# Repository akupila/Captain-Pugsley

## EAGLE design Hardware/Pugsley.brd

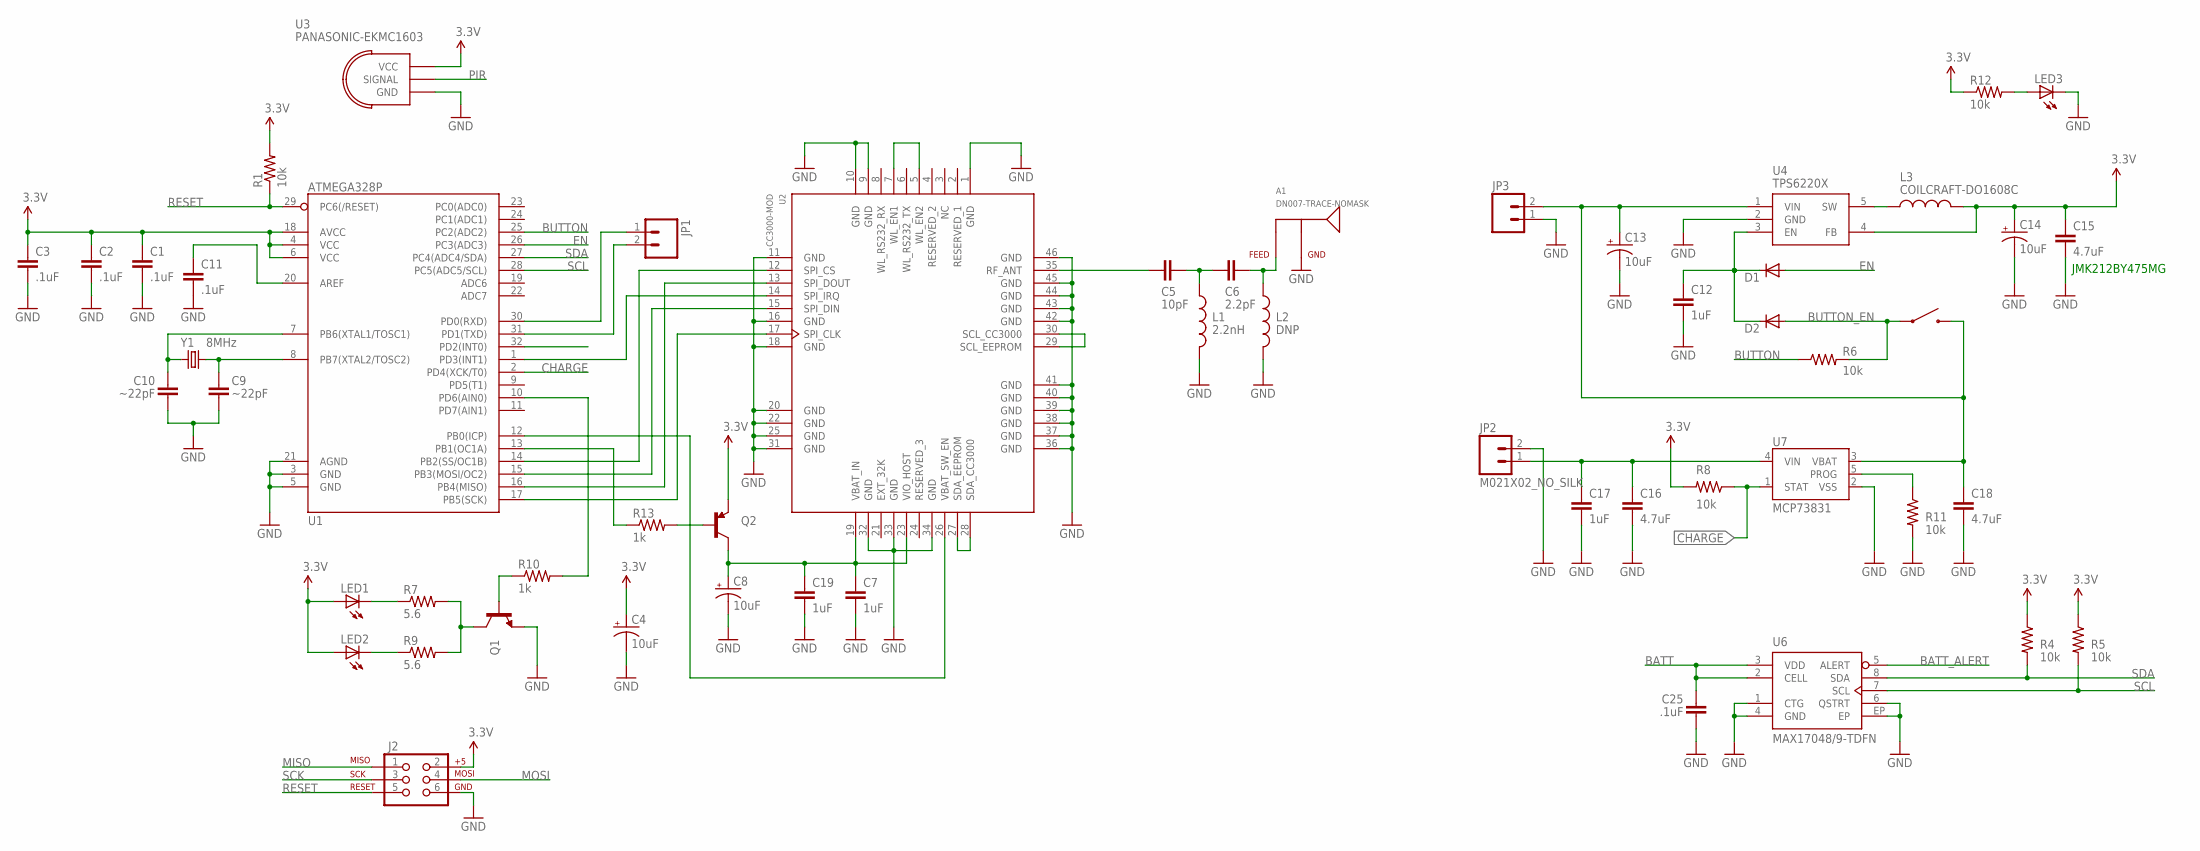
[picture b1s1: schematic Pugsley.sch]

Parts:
A1: DN007-TRACE-NOMASK
C1, C2, C3, C11, C25: .1uF; 0402-CAP
C4, C8, C13, C14: 10uF; EIA3216
C5: 10pF; 0402-CAP
C6: 2.2pF; 0402-CAP
C7, C12, C17, C19: 1uF; 0402-CAP
C9, C10: ~22pF; 0402-CAP
C15, C16, C18: 4.7uF; 0805
D1, D2: DIODESOD; SOD-323
J2: AVR_SPI_PRG_6NS; 2X3-NS
JP1, JP2, JP3: M021X02_NO_SILK; 1X02_NO_SILK
L1: 2.2nH; C0402
L2: DNP; C0402
L3: COILCRAFT-DO1608C
LED1, LED2, LED3: LED0603; LED-0603
Q1: TRANSISTOR_NPNSOT23; SOT23
Q2: TRANSISTOR_PNPSMD; SOT23-3
R1, R4, R5, R6, R8, R11, R12: 10k; 0402-RES
R7, R9: 5.6; 0402-RES
R10, R13: 1k; 0402-RES
S1: C&K-KSR2XX
U1: ATMEGA328P; TQFP32-08
U2: CC3000-MOD; CC3000
U3: PANASONIC-EKMC1603; PIR-PANASONIC-EKMC1603XXX
U4: TPS6220X; SOT23-5
U6: MAX17048/9-TDFN; TDFN-8
U7: MCP73831; SOT23-5
Y1: 8MHz; CRYSTAL-SMD-5X3

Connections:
3.3V: C1.1, C2.1, C3.1, C4.A (+), C14.A (+), C15.1, J2.2, L3.2, LED1.A, LED2.A, Q2.2 (E), R1.2, R4.1, R5.1, R8.2, R12.1, U1.4 (VCC), U1.6 (VCC), U1.18 (AVCC), U3.VDD (VCC), U4.4 (FB)
BATT: C13.A (+), C18.1, C25.1, JP3.2, S1.P$2 (2), U4.1 (VIN), U6.2 (CELL), U6.3 (VDD), U7.3 (VBAT)
BATT_ALERT: U6.5 (ALERT)
BUTTON: R6.1, U1.25 (PC2(ADC2))
BUTTON_EN: D2.2 (A), R6.2, S1.P$1 (1)
CHARGE: R8.1, U1.2 (PD4(XCK/T0)), U7.1 (STAT)
EN: D1.2 (A), U1.26 (PC3(ADC3))
GND: A1.GND@1 (GND), A1.GND@2 (GND), C1.2, C2.2, C3.2, C4.C (-), C7.2, C8.C (-), C9.2, C10.2, C11.2, C12.2, C13.C (-), C14.C (-), C15.2, C16.2, C17.2, C18.2, C19.2, C25.2, J2.6, JP2.2, JP3.1, L1.2, L2.2, LED3.C, Q1.2 (E), R11.2, U1.3 (GND), U1.5 (GND), U1.21 (AGND), U2.1 (GND), U2.9 (GND), U2.10 (GND), U2.11 (GND), U2.16 (GND), U2.18 (GND), U2.20 (GND), U2.22 (GND), U2.25 (GND), U2.31 (GND), U2.32 (GND), U2.33 (GND), U2.34 (GND), U2.36 (GND), U2.37 (GND), U2.38 (GND), U2.39 (GND), U2.40 (GND), U2.41 (GND), U2.42 (GND), U2.43 (GND), U2.44 (GND), U2.45 (GND), U2.46 (GND), U3.GND, U4.2 (GND), U6.1 (CTG), U6.4 (GND), U6.6 (QSTRT), U6.EP, U7.2 (VSS)
LED: R10.2, U1.10 (PD6(AIN0))
MISO: J2.1, U1.16 (PB4(MISO)), U2.13 (SPI_DOUT)
MOSI: J2.4, U1.15 (PB3(MOSI/OC2)), U2.15 (SPI_DIN)
unnamed: C11.1, U1.20 (AREF)
unnamed: C5.2, U2.35 (RF_ANT)
unnamed: Q1.1 (B), R10.1
unnamed: C12.1, D1.1 (C), D2.1 (C), U4.3 (EN)
unnamed: L3.1, U4.5 (SW)
unnamed: U1.1 (PD3(INT1)), U2.14 (SPI_IRQ)
unnamed: R11.1, U7.5 (PROG)
unnamed: U2.29 (SCL_EEPROM), U2.30 (SCL_CC3000)
unnamed: C5.1, C6.2, L1.1
unnamed: A1.FEED, C6.1, L2.1
unnamed: U2.27 (SDA_EEPROM), U2.28 (SDA_CC3000)
unnamed: LED1.C, R7.1
unnamed: C9.1, U1.8 (PB7(XTAL2/TOSC2)), Y1.3 (2)
unnamed: U2.5 (WL_EN2), U2.7 (WL_EN1)
unnamed: C10.1, U1.7 (PB6(XTAL1/TOSC1)), Y1.1
unnamed: C7.1, C8.A (+), C19.1, Q2.3 (C), U2.19 (VBAT_IN), U2.23 (VIO_HOST)
unnamed: Q1.3 (C), R7.2, R9.2
unnamed: LED2.C, R9.1
unnamed: LED3.A, R12.2
unnamed: Q2.1 (B), R13.2
PIR: U1.32 (PD2(INT0)), U3.OUT (SIGNAL)
RESET: J2.5, R1.1, U1.29 (PC6(/RESET))
RX: JP1.1, U1.30 (PD0(RXD))
SCK: J2.3, U1.17 (PB5(SCK)), U2.17 (SPI_CLK)
SCL: R5.2, U1.28 (PC5(ADC5/SCL)), U6.7 (SCL)
SDA: R4.2, U1.27 (PC4(ADC4/SDA)), U6.8 (SDA)
TX: JP1.2, U1.31 (PD1(TXD))
VIN: C16.1, C17.1, JP2.1, U7.4 (VIN)
WIFI_CS: U1.14 (PB2(SS/OC1B)), U2.12 (SPI_CS)
WIFI_EN: U1.12 (PB0(ICP)), U2.26 (VBAT_SW_EN)
WIFI_PWR: R13.1, U1.13 (PB1(OC1A))

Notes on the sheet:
JMK212BY475MG

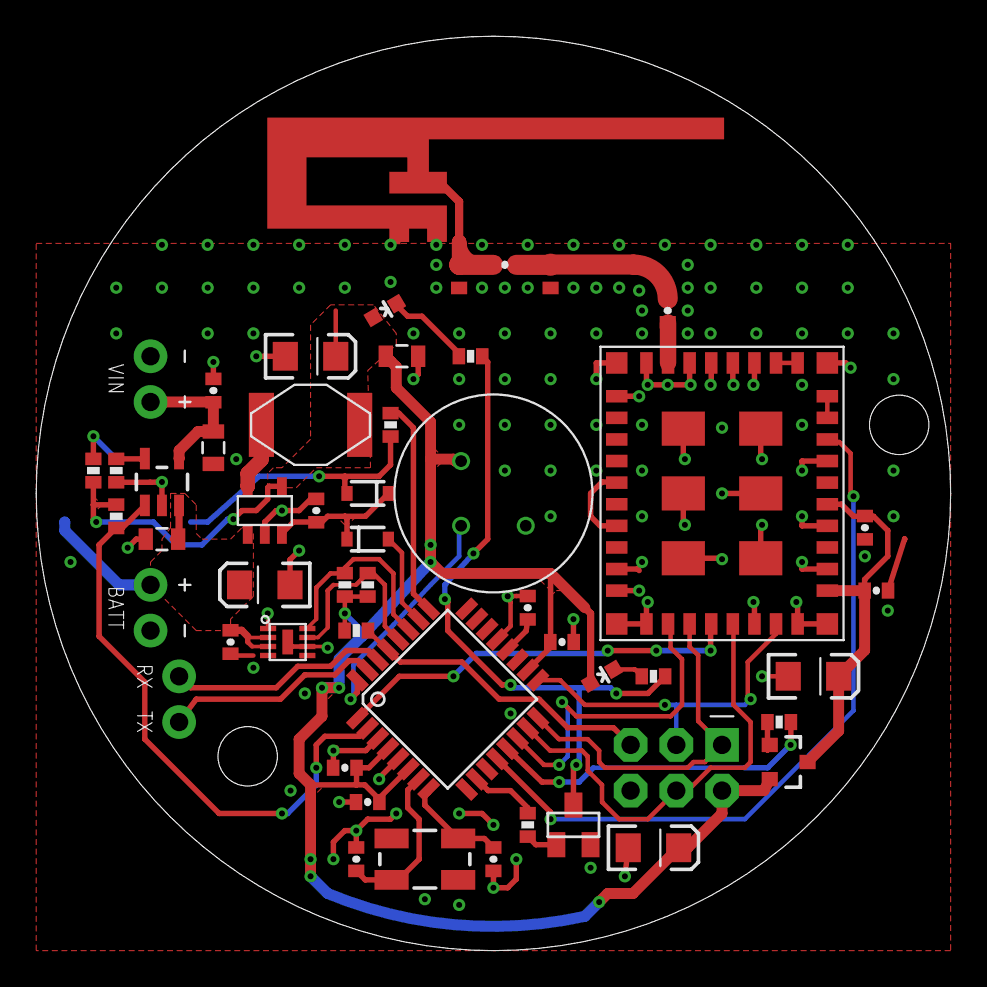
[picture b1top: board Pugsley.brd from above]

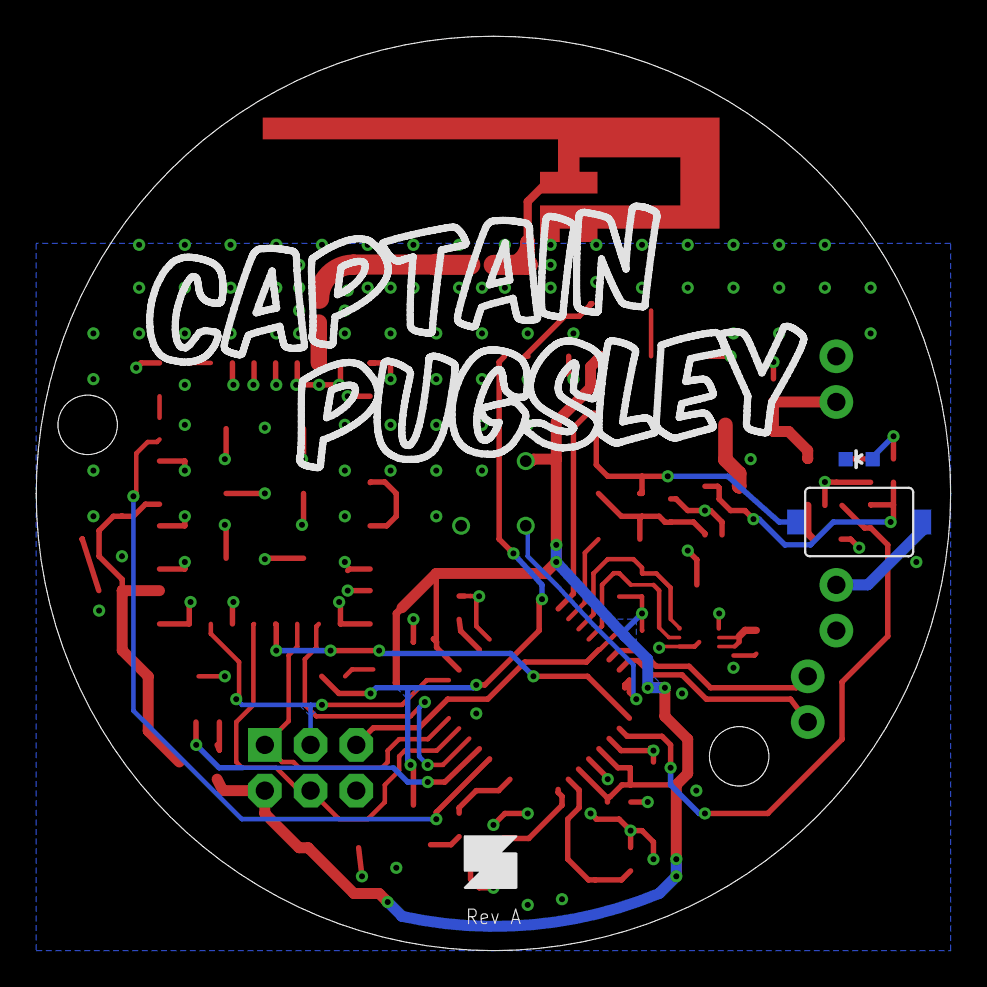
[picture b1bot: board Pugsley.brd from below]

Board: 2 copper layers, 50.8 x 50.8 mm, 56 parts (3 on the bottom side), 41 nets.

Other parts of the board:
U$1, U$2: STAND-OFF

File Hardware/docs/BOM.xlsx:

Item # | Quantity | Ref des | Value | Package | Description | Manufacturer | Mfg part # | Reseller | Cost (x1) | Cost (x10) | Cost (x100) | Required x 3 | In cart | Comments
1 | 5 | C1, C2, C3, C11, C25 | 0.1uF | 0402 | Decoupling capacitor | TDK Corporation | C1005X7R1C104K050BC | Digikey | 0.08 | 2.1999999999999999E-2 | 1.01E-2 | 15 | 100
2 | 5 | C4, C5, C8, C13, C14 | 10uF | 1206 |  | Kemet | T491A106K006AT7280 | Digikey | 0.27 | 0.23499999999999999 | 0.1174 | 15 | 15
3 | 1 | C6 | 2.2pF | 0402 | RF matching | Johanson Technology Inc | 500R07S2R2BV4T | Digikey | 0.21 | 0.17799999999999999 | 8.8800000000000004E-2 | 3 | 9
4 | 4 | C7, C12, C17, C19 | 1uF | 0402 |  | TDK Corporation | C1005X5R0J105K050BB | Digikey | 0.08 | 3.3000000000000002E-2 | 1.52E-2 | 12 | 100
5 | 2 | C9, C10 | 22pF | 0402 |  | Yageo | CC0402JRNPO9BN220 | Digikey | 0.08 | 1.0999999999999999E-2 | 5.0000000000000001E-3 | 6 | 100
6 | 3 | C15, C16, C18 | 4.7uF | 0805 |  | Samsung Electro-Mechanics | CL21A475KOFNNNE | Digikey | 0.12 | 7.9000000000000001E-2 | 3.7499999999999999E-2 | 9 | 100
7 | 2 | D1, D2 | Diode | SOD-323 |  | Fairchild Semiconductor | 1N4148WS | Digikey | 0.11 | 9.9000000000000005E-2 | 6.8400000000000002E-2 | 6 | n/a (~30 In stock)
8 | 1 | L1 | 2.2nH | 0402 | RF matching | Johanson Technology Inc | L-07C2N2SV6T | Digikey | 0.08 | 4.1000000000000002E-2 | 2.8899999999999999E-2 | 3 | 10
9 | 1 | L3 | 6.8-10uH |  |  | Coilcraft | DO1608C-822MLB | Farnell | 1.03 | 0.95199999999999996 | 0.76400000000000001 | 3 | 3
10 | 3 | LED1, LED2, LED3 | White | 0603 |  |  |  |  |  |  |  | 9
11 | 1 | Q1 | NPN | SOT-23 |  | NXP Semiconductors | MMBT3904,215 | Digikey | 0.08 | 7.8E-2 | 5.0999999999999997E-2 | 3 | 25
12 | 1 | Q2 | PNP | SOT-23 |  | NXP Semiconductors | PBSS4041PT,215 | Digikey | 0.38 | 0.312 | 0.24129999999999999 | 3 | 10
13 | 7 | R1, R2, R3, R4, R8, R11, R12 | 10k | 0402 |  | Yageo | RC0402FR-0710KL | Digikey | 0.08 | 1.2E-2 | 4.8999999999999998E-3 | 21 | 100
14 | 2 | R7, R9 | 5.6r | 0402 |  | Panasonic Electronic Components | ERJ-2GEJ5R6X | Digikey | 0.08 | 1.14E-2 | 8.6E-3 | 6 | 100
15 | 2 | R10, R13 | 1k | 0402 |  | Panasonic Electronic Components | ERJ-2RKF1001X | Digikey | 0.08 | 1.6199999999999999E-2 | 1.2200000000000001E-2 | 6 | 50
16 | 1 | S1 | SPST | SMT |  | C&K Components | KSR231GLFS | Digikey | 0.56000000000000005 | 0.53800000000000003 | 0.43930000000000002 | 3 | 5
17 | 1 | U1 | ATMEGA328P | TQFP-32 |  | Atmel | ATMEGA328P-AUR | Digikey | 3.16 | 2.8319999999999999 | 2.3161 | 3 | in stock
18 | 1 | U2 | CC3000 | SMT |  | Texas Instruments | CC3000MOD | Digikey | 11.91 | 11.91 | 11.91 | 3 | 2
19 | 1 | U3 | EKMC1603 |  |  | Panasonic |  | Farnell | 7.96 | 7.96 | 6.66 | 3 | 1 in stock
20 | 1 | U4 | TPS62203 | SOT-23-5 |  | Texas Instruments | TPS62203DBVT | Digikey | 1.6 | 1.4490000000000001 | 1.1671 | 3 | 3
21 | 1 | U5 | MAX17048 | SOT-23-5 |  | Maxim Integrated | MAX17048G+ | Mouser | 2.15 | 1.96 | 1.47 | 3 | in stock
22 | 1 | U6 | MCP73831 | TDFN-8 |  | Microchip Technology | MCP73831T-2ACI/OT | Digikey | 0.55000000000000004 | 0.46 | 0.3453 | 3 | 5
23 | 1 | Y1 | 8MHz | 4-SMD |  | TXC Corporation | 7B-8.000MAAJ-T | Digikey | 0.67 | 0.59699999999999998 | 0.49320000000000003 | 3 | in stock
23 | 48 |  |  |  |  |  |  |  | 34.03 | 31.280200000000004 | 27.008500000000005

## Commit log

2014-08-14 Initial import. Hardware ordered from OSHPark
2014-08-14 Added PDF schematic
2014-08-19 Added BOM

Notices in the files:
parts and their libraries:
SparkFun-DigitalIC: Licensing: Creative Commons ShareAlike 4.0 International - https://creativecommons.org/licenses/by-sa/4.0
